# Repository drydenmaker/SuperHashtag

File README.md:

# SuperHashtag
a custom PCB for #badgelife and #badgeLove

This is an ultra simple starting place for those wanting to get involved with the phenomenon that is #badgelife.

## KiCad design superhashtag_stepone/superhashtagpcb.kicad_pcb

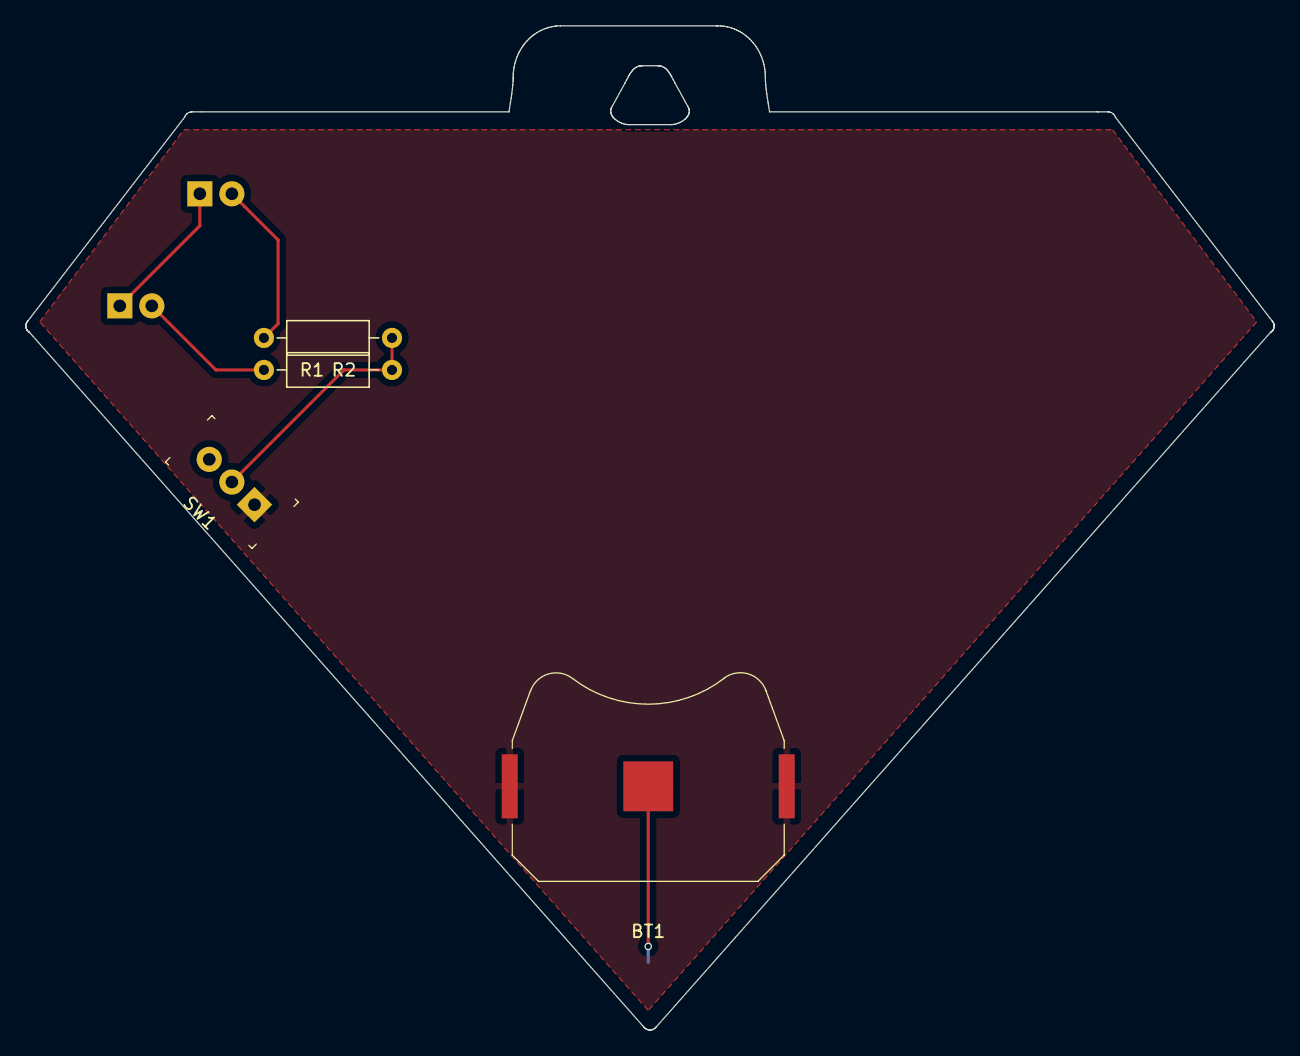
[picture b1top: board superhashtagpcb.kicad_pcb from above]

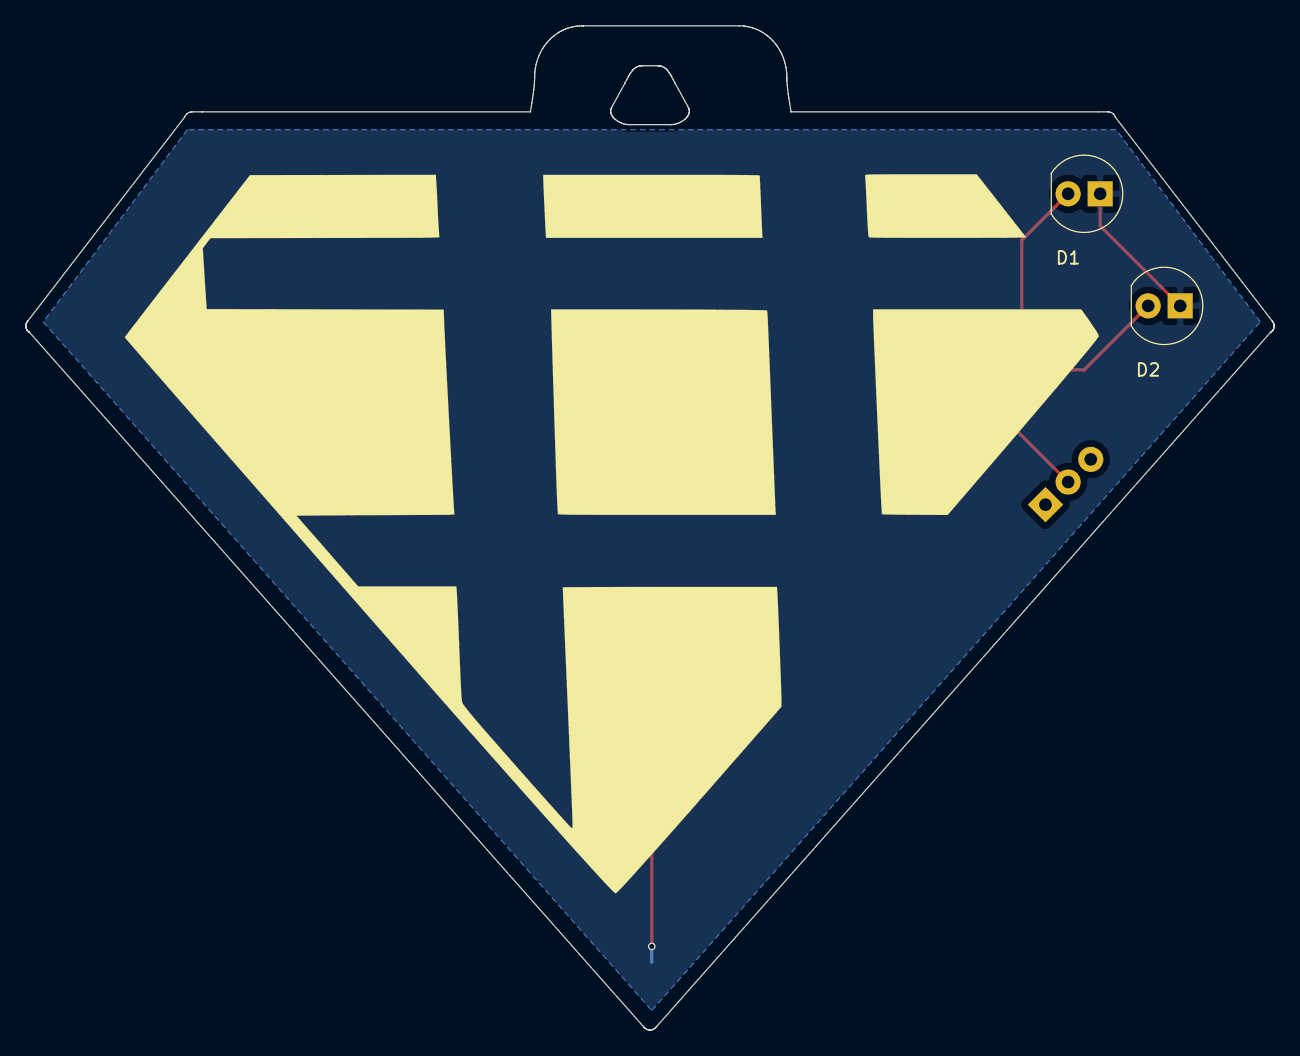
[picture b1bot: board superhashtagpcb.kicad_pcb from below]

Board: 2 copper layers, 99.0 x 79.6 mm, 6 parts (2 on the bottom side), 5 nets.

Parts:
BT1: Battery; BatteryHolder_Keystone_3034_1x20mm
D1, D2: LED; LED_5mm_Radial
R1, R2: R; R_Axial_DIN0207_L6.3mm_D2.5mm_P10.16mm_Horizontal
SW1: SW_DPDT_x2; Switch_Toggle_ATE1D-2M3-10-Z

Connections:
/VCC: BT1.1, SW1.1
GND: BT1.2, D1.1, D2.1
unnamed: D1.2, R1.2
unnamed: D2.2, R2.2
unnamed: R1.1, R2.1, SW1.2

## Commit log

2019-01-21 first simple drawing
2019-01-21 exporting kicad files from svg
2019-02-03 adding lanyard hole and renaming files
2019-02-03 adding schema and layout position changes.
2019-02-03 mapping footprints
2019-02-09 initial layout, pre coper
2019-02-10 placed traces and vias
2019-02-10 adding readme
2019-02-10 adding pic of project
2019-02-24 renaming initial sub directory
2019-02-24 doing some more renaming and duplicating the next chapter source
2019-05-25 adding half baked H+H badge and initial H+H SAO
2019-05-25 renaming sao svg
2019-05-25 renaming base svg
2019-05-25 adding pcb and more graphics on sao
2019-05-25 adding b silk making slots smaller
2019-05-25 rerouted sao
2019-05-25 adding mounting hole connectors
2019-06-08 first prototype gerbers
2019-07-23 Hth mk2 (#1)
    * moving edge cuts to make front and back smaller
    * adding front silk to minimize light leak through mask
    * index layers for resize
    * resized
    * distributed layers and refill black
    * generated new pcb from svg
